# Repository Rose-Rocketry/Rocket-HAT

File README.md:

# Rocket-HAT
A Sensor Hat for a raspberry pi with: an IMU, Altimeter, and 5V power protection

# Usage
There are two jumpers on the board; J7 is for powering the hat through the PI. Otherwise, the HAT will get power from the battery while also powering the Pi. J9 is to
enable writing to the EEPROM after manufacture. This EEPROM is for matching with the Raspberry Pi foundation's specs.

There is also a solder bridge for the BNO055. This is in case we have an address conflict and need to change the address from 0x28 to 0x29.

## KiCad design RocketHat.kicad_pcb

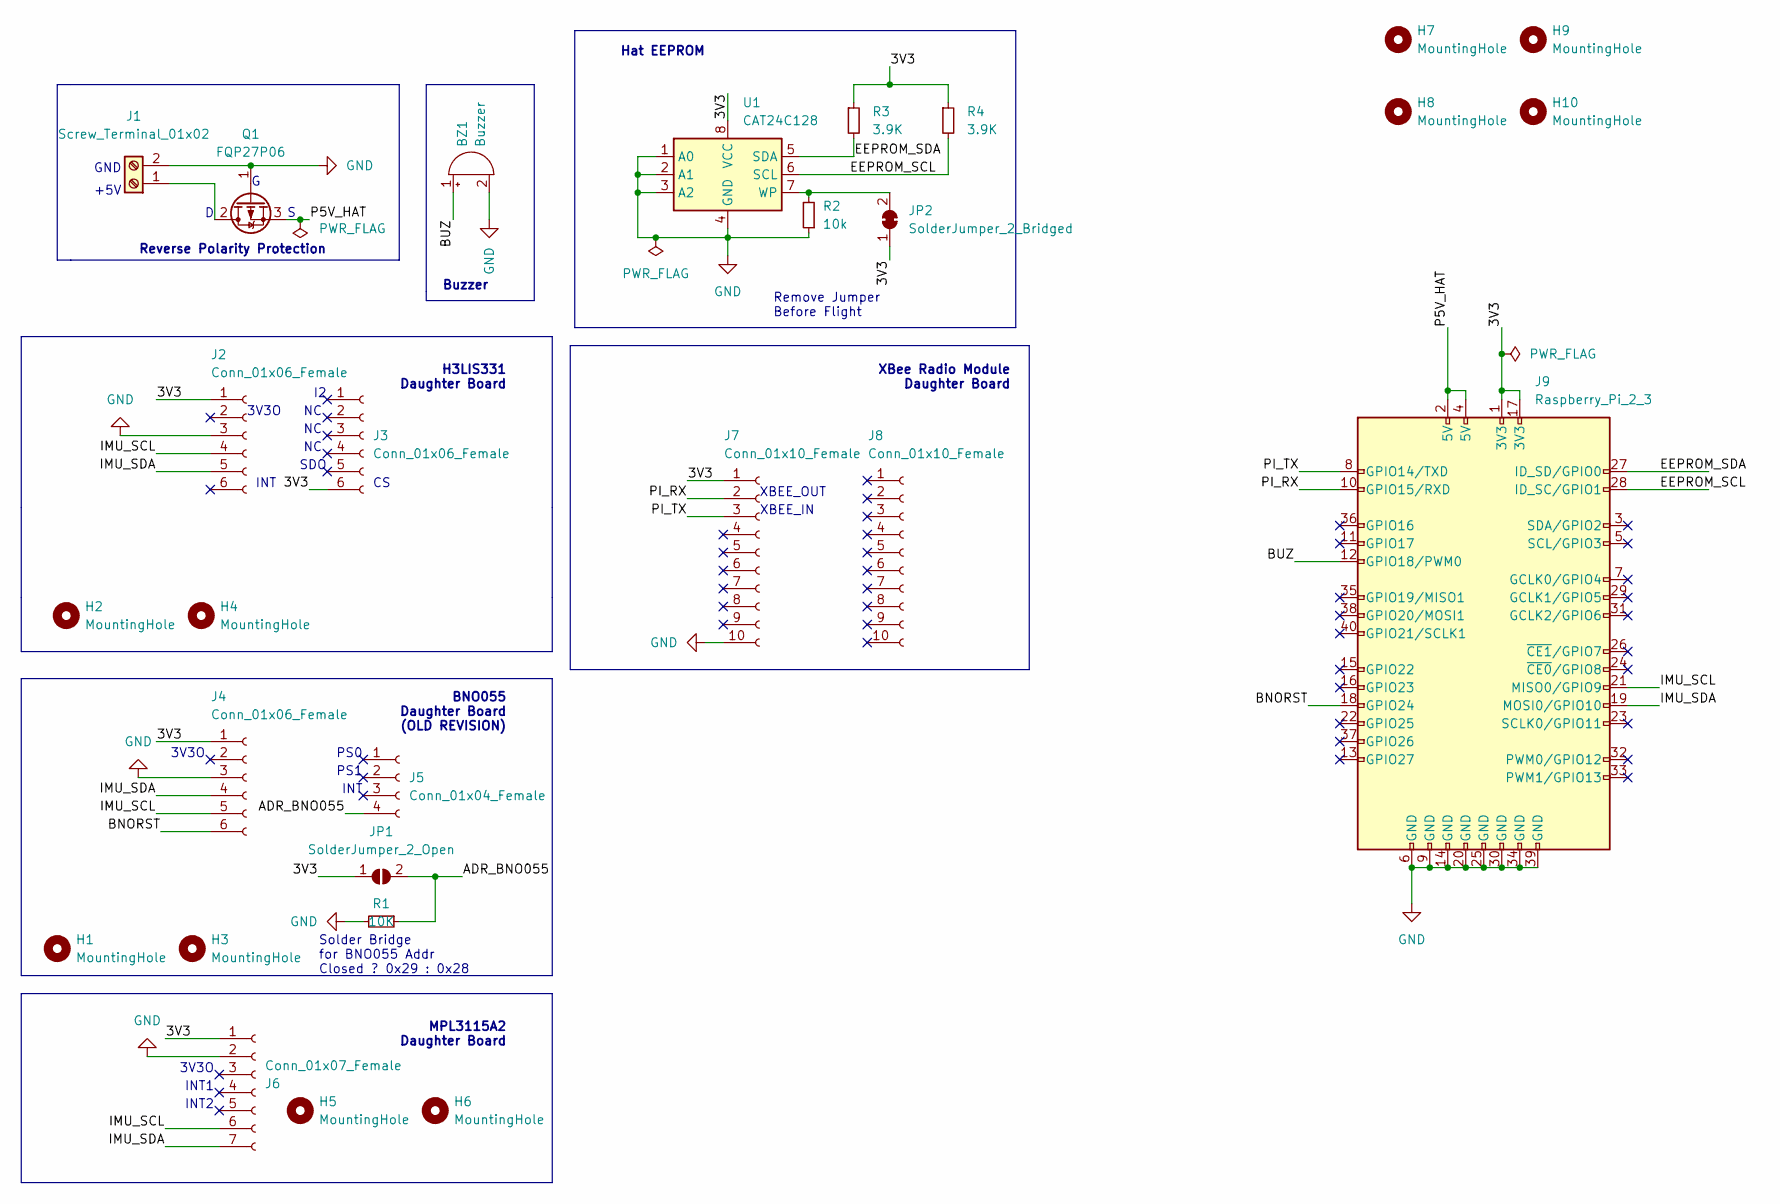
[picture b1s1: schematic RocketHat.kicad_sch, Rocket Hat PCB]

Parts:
BZ1: Buzzer; Buzzer_TDK_PS1240P02BT_D12.2mm_H6.5mm
H1, H2, H3, H4, H5, H6: MountingHole; MountingHole_2.2mm_M2
H7, H8, H9, H10: MountingHole; MountingHole_2.7mm_M2.5
J1: Screw_Terminal_01x02; TerminalBlock_Phoenix_MKDS-1,5-2_1x02_P5.00mm_Horizontal
J2, J3, J4: Conn_01x06_Female; PinSocket_1x06_P2.54mm_Vertical
J5: Conn_01x04_Female; PinSocket_1x04_P2.54mm_Vertical
J6: Conn_01x07_Female; PinSocket_1x07_P2.54mm_Vertical
J7, J8: Conn_01x10_Female; PinSocket_1x10_P2.00mm_Vertical
J9: Raspberry_Pi_2_3; PinSocket_2x20_P2.54mm_Vertical
JP1: SolderJumper_2_Open; SolderJumper-2_P1.3mm_Open_TrianglePad1.0x1.5mm
JP2: SolderJumper_2_Bridged; SolderJumper-2_P1.3mm_Bridged_RoundedPad1.0x1.5mm
Q1: FQP27P06; TO-220-3_Vertical
R1: 10K; R_Axial_DIN0204_L3.6mm_D1.6mm_P5.08mm_Horizontal
R2: 10k; R_Axial_DIN0204_L3.6mm_D1.6mm_P5.08mm_Horizontal
R3, R4: 3.9K; R_Axial_DIN0204_L3.6mm_D1.6mm_P5.08mm_Horizontal
U1: CAT24C128; SOIC-8_3.9x4.9mm_P1.27mm

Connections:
/3V3: J2.1, J3.6, J4.1, J6.1, J7.1, J9.1 (3V3), J9.17 (3V3), JP1.1 (A), JP2.1 (A), R3.1, R4.1, U1.8 (VCC)
/ADR_BNO055: J5.4, JP1.2 (B), R1.1
/BNORST: J4.6, J9.18 (GPIO24)
/BUZ: BZ1.1 (-), J9.12 (GPIO18/PWM0)
/EEPROM_SCL: J9.28 (ID_SC/GPIO1), R4.2, U1.6 (SCL)
/EEPROM_SDA: J9.27 (ID_SD/GPIO0), R3.2, U1.5 (SDA)
/IMU_SCL: J2.4, J4.5, J6.6, J9.21 (MISO0/GPIO9)
/IMU_SDA: J2.5, J4.4, J6.7, J9.19 (MOSI0/GPIO10)
/P5V_HAT: J9.2 (5V), J9.4 (5V), Q1.3 (S)
/PI_RX: J7.2, J9.10 (GPIO15/RXD)
/PI_TX: J7.3, J9.8 (GPIO14/TXD)
GND: BZ1.2 (+), J1.2, J2.3, J4.3, J6.2, J7.10, J9.6 (GND), J9.9 (GND), J9.14 (GND), J9.20 (GND), J9.25 (GND), J9.30 (GND), J9.34 (GND), J9.39 (GND), Q1.1 (G), R1.2, R2.1, U1.1 (A0), U1.2 (A1), U1.3 (A2), U1.4 (GND)
unnamed: J1.1, Q1.2 (D)
unnamed: JP2.2 (B), R2.2, U1.7 (WP)

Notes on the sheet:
Buzzer
XBEE_IN
PS1
Reverse Polarity Protection
INT
XBEE_OUT
MPL3115A2 Daughter Board
INT1
3V3O
GND
XBee Radio Module Daughter Board
Remove Jumper Before Flight
H3LIS331 Daughter Board
BNO055 Daughter Board (OLD REVISION)
+5V
Hat EEPROM
Solder Bridge for BNO055 Addr Closed ? 0x29 : 0x28
INT2
PS0
SDO

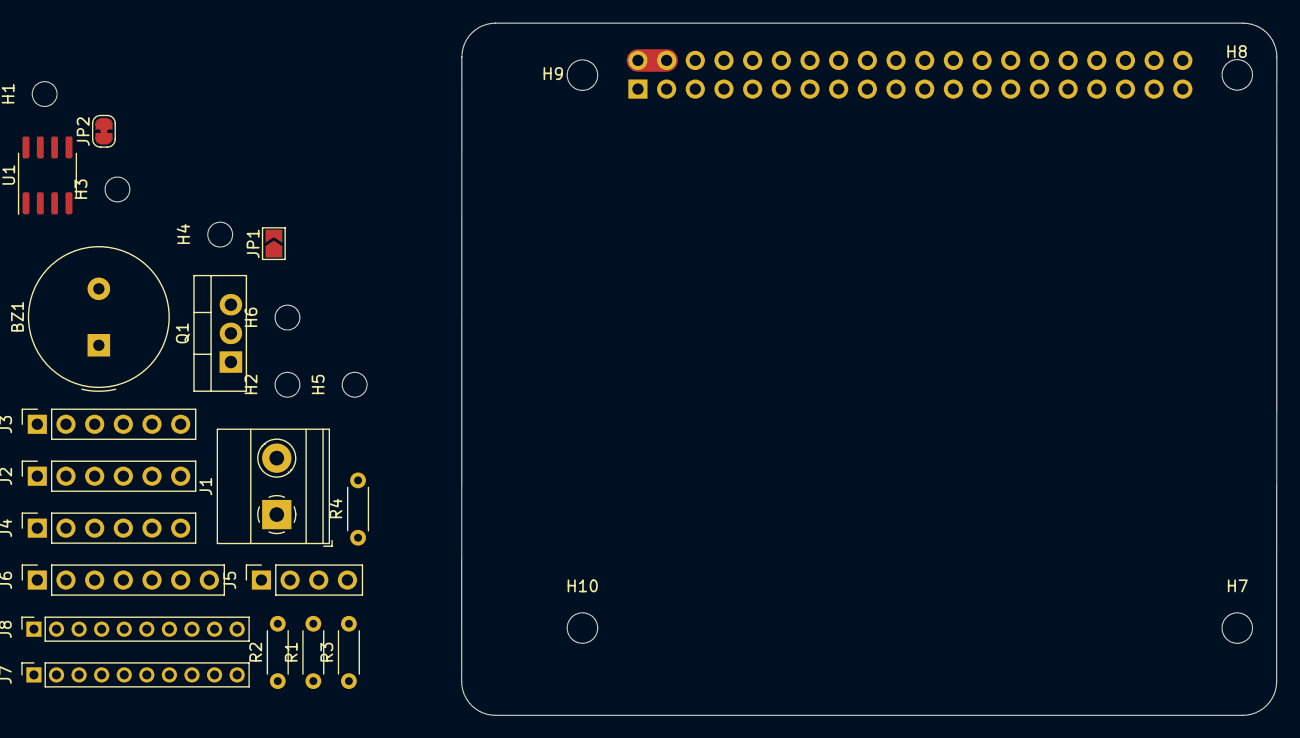
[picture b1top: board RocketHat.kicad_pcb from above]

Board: 2 copper layers, 72.2 x 61.3 mm, 28 parts (1 on the bottom side), 14 nets.

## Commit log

2022-02-14 Uploaded KiCad Files
2022-02-14 Fixed Missing Line
2022-02-14 Added Resources
2022-02-14 Cleaned Up Layouts A Little
2022-02-14 Fixed All DRC Errors
2022-02-14 Fixed Segments
2022-02-14 Fixed location of Mounting Holes
2022-02-14 Generated Gerbers for Curiosity
2022-02-15 Set Mounting Holes 1&2 to M2
2022-02-15 Added Flood Zone
2022-02-15 Added pi code
2022-02-15 Backups
2022-02-21 Added Gerber Zip
2022-02-21 Smol Board
2022-02-21 Even SMOLLER Board
2022-02-21 Smol Board + Title Block
2022-03-08 Rose Rocketry Raspy Rasputin github account created 03/08/2022 Added the updated IMU code
2022-03-08 added imu code
2022-03-10 Backups & Excel
2022-03-10 We made changes
2022-03-11 I have made it so that the datafiles are uploaded to git as well
2022-03-11 fixed the accel_p error since it isn't needed anymore
2022-03-11 ok here we go again
2022-03-14 Added Final BOM Table
2022-03-16 sfjsdlfjsalfjsldfjalsf
2022-03-16 no csv
2022-03-16 FLIP H3L!!!!
2022-03-16 changed datafile format
2022-03-20 Version 1.1.0
2022-03-20 Added Graphic
2022-03-21 Token
2022-03-24 PCB Updates
2022-03-25 Finished the drone flight test
2022-03-25 Cool Thicc Lines
2022-03-25 Fixed DRC
2022-04-02 Fixed Inverted Layout
2022-04-03 Passed DRC With 1.1.1
2022-04-07 Recovered From Payload: Python
2022-04-07 Got GRC File
    Blame Everest if not right
2022-04-21 Added Buzzer
2022-04-22 Updated EEPROM WP
2022-04-22 Updated Schematics and Footprints
2022-04-22 Added Mounting Holes for all sensors
2022-04-28 Cleared Layout
2022-04-28 Closed KiCad
2022-09-26 Create LICENSE

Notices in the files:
RocketHat.kicad_pcb:
https://creativecommons.org/licenses/by-sa/4.0
License: CC BY-SA 4.0
